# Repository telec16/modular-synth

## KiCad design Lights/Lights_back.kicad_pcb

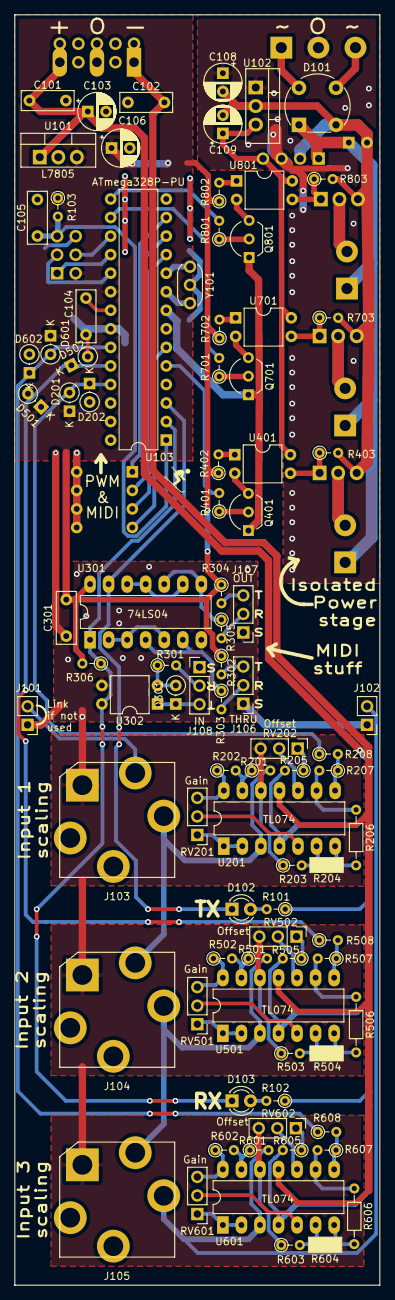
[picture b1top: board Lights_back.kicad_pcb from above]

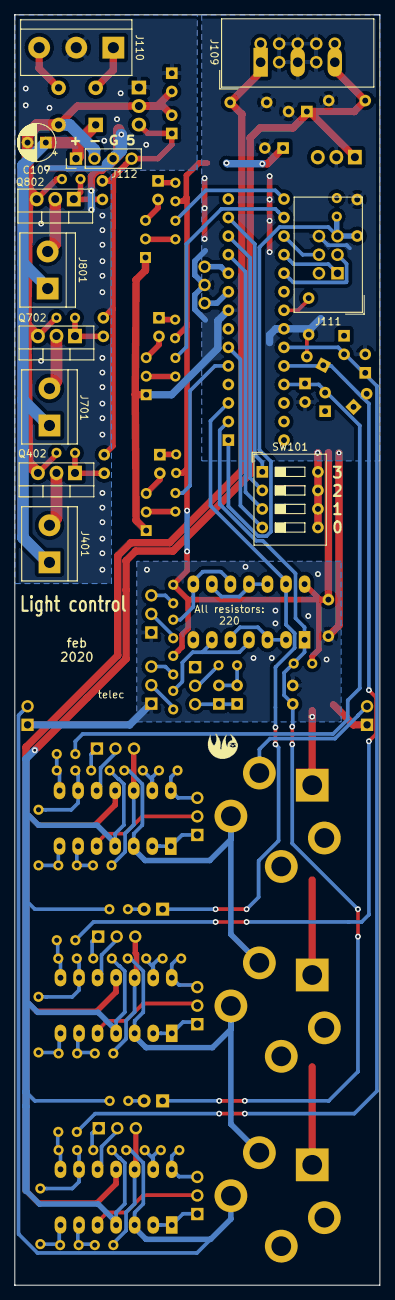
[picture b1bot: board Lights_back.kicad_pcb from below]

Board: 2 copper layers, 50.0 x 174.0 mm, 102 parts (12 on the bottom side), 91 nets.

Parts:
C101, C102, C104, C105, C301: 100n; C_Disc_D7.0mm_W2.5mm_P5.00mm
C103, C106, C108, C109: 1u; CP_Radial_D5.0mm_P2.50mm
C107: 10u; CP_Radial_D5.0mm_P2.50mm
D101: D_Bridge_+-AA; Diode_Bridge_Round_D8.9mm
D102, D103: LED; LED_D3.0mm_FlatTop
D201, D202, D301, D501, D502, D601, D602: 1N4148; D_DO-35_SOD27_P2.54mm_Vertical_KathodeUp
J101: chain_in; PinHeader_1x02_P2.54mm_Vertical
J102: chain_out; PinHeader_1x02_P2.54mm_Vertical
J103: Input1; Jack_6.35mm_PJ_629HAN
J104: Input2; Jack_6.35mm_PJ_629HAN
J105: Input3; Jack_6.35mm_PJ_629HAN
J106: THRU; PinHeader_TRS_P2.54mm_Vertical
J107: OUT; PinHeader_TRS_P2.54mm_Vertical
J108: IN; PinHeader_TRS_P2.54mm_Vertical
J109: EuroPower
J110: ExternalPower; TerminalBlock_bornier-3_P5.08mm
J111: Programming; IDC-Header_2x03_P2.54mm_Vertical
J112: chain_power; PinHeader_1x04_P2.54mm_Vertical
J401, J701, J801: Light; TerminalBlock_bornier-2_P5.08mm
Q401, Q701, Q801: PN2222A; TO-92_Inline_Wide
Q402, Q702, Q802: IRF540N; TO-220-3_Vertical
R101, R102: 1K; R_Axial_DIN0204_L3.6mm_D1.6mm_P2.54mm_Vertical
R103: 22k; R_Axial_DIN0204_L3.6mm_D1.6mm_P2.54mm_Vertical
R201, R202, R203, R205, R207, R501, R502, R503, R505, R507, R601, R602, R603, R605, R607: 100k; R_Axial_DIN0204_L3.6mm_D1.6mm_P2.54mm_Vertical
R204, R504, R604: 200k; R_Axial_DIN0204_L3.6mm_D1.6mm_P2.54mm_Vertical
R206, R506, R606: 100k; R_Axial_DIN0204_L3.6mm_D1.6mm_P7.62mm_Horizontal
R208, R401, R403, R508, R608, R701, R703, R801, R803: 1k; R_Axial_DIN0204_L3.6mm_D1.6mm_P2.54mm_Vertical
R301, R302, R303, R304, R305, R306: 220; R_Axial_DIN0204_L3.6mm_D1.6mm_P2.54mm_Vertical
R402, R702, R802: 100; R_Axial_DIN0204_L3.6mm_D1.6mm_P2.54mm_Vertical
RV201, RV202, RV501, RV502, RV601, RV602: 100k; PinHeader_1x03_P2.54mm_Vertical
SW101: MIDI_settings; SW_DIP_SPSTx04_Slide_9.78x12.34mm_W7.62mm_P2.54mm
U101, U102: L7805; TO-220-3_Vertical
U103: ATmega328P-PU; DIP-28_W7.62mm
U201, U501, U601: TL074; DIP-14_W7.62mm_LongPads
U301: 74LS04; DIP-14_W7.62mm_LongPads
U302, U401, U701, U801: 6N138; DIP-4_W7.62mm
Y101: 16MHz; Resonator-3Pin_W6.0mm_H3.0mm

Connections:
+5V: C106.1, C301.2, D201.1, D501.1, D601.1, J111.2, R103.1, R302.1, R304.1, R306.2, R402.1, R702.1, R802.1, U101.3, U103.7, U103.20, U301.14
+5VP: C109.1, J112.4, U102.3, U401.4, U701.4, U801.4
+12V: C101.2, C103.1, J109.3, R101.1, R102.1, R205.2, R505.2, R605.2, U101.1, U201.4, U501.4, U601.4
+VDC: C107.1, D101.1, J112.1, J401.1, J701.1, J801.1
-12V: C102.2, J109.1, U201.11, U501.11, U601.11
-VDC: C107.2, C108.2, C109.2, D101.2, J112.2, Q402.3, Q702.3, Q802.3, R403.2, R703.2, R803.2, U102.2
/ADC1: D201.2, D202.1, R208.1, U103.25
/ADC2: D501.2, D502.1, R508.1, U103.24
/ADC3: D601.2, D602.1, R608.1, U103.23
/MIDI/MIDI_IN+: D301.1, J108.T, U302.1
/MIDI/MIDI_IN-: J108.R, R301.2
/MIDI/MIDI_OUT+: J107.T, R304.2
/MIDI/MIDI_OUT-: J107.R, R305.2
/MIDI/MIDI_THRU+: J106.T, R302.2
/MIDI/MIDI_THRU-: J106.R, R303.2
/MIDI_IN: D103.1, R306.1, U103.2, U301.1, U302.4
/MIDI_OUT: D102.1, U103.3, U301.13
/MISO: J111.1, U103.18
/MOSI: J111.4, U103.17
/Normalize/In: J103.T, J104.TN, R201.2, U201.3
/PWM1: R801.2, U103.15
/PWM2: R701.2, U103.16
/PWM3: R401.2, U103.5
/SCK: J111.3, U103.19
/sheet606D67AE/In: J102.2, J105.T, R601.2, U601.3
/sheet606D2594/In: J104.T, J105.TN, R501.2, U501.3
/~RESET: C105.2, J111.5, R103.2, U103.1
GND: C101.1, C102.1, C103.2, C104.1, C105.1, C106.2, C301.1, D202.2, D502.2, D602.2, J101.1, J102.1, J103.S, J104.S, J105.S, J106.S, J107.S, J109.2, J111.6, Q401.1, Q701.1, Q801.1, R203.1, R503.1, R603.1, RV202.3, RV502.3, RV602.3, SW101.5, SW101.6, SW101.7, SW101.8, U101.2, U103.8, U103.22, U201.12, U301.7, U302.3, U501.12, U601.12, Y101.2
GNDPWR: C108.1, J110.2, J112.3, U102.1
unnamed: C104.2, U103.21
unnamed: D101.3, J110.3
unnamed: D101.4, J110.1
unnamed: D102.2, R101.2
unnamed: D103.2, R102.2
unnamed: D301.2, R301.1, U302.2
unnamed: J101.2, J103.TN
unnamed: J401.2, Q402.2
unnamed: J701.2, Q702.2
unnamed: J801.2, Q802.2
unnamed: Q401.2, R401.1
unnamed: Q401.3, U401.2
unnamed: Q402.1, R403.1, U401.3
unnamed: Q701.2, R701.1
unnamed: Q701.3, U701.2
unnamed: Q702.1, R703.1, U701.3
unnamed: Q801.2, R801.1
unnamed: Q801.3, U801.2
unnamed: Q802.1, R803.1, U801.3
unnamed: R201.1, R202.2, U201.13
unnamed: R202.1, RV201.3, U201.14
unnamed: R203.2, R204.1, U201.6
unnamed: R204.2, R206.2, U201.7
unnamed: R205.1, RV202.1
unnamed: R206.1, R207.2, U201.9
unnamed: R207.1, R208.2, U201.8
unnamed: R303.1, U301.4, U301.6
unnamed: R305.1, U301.8, U301.10
unnamed: R402.2, U401.1
unnamed: R501.1, R502.2, U501.13
unnamed: R502.1, RV501.3, U501.14
unnamed: R503.2, R504.1, U501.6
unnamed: R504.2, R506.2, U501.7
unnamed: R505.1, RV502.1
unnamed: R506.1, R507.2, U501.9
unnamed: R507.1, R508.2, U501.8
unnamed: R601.1, R602.2, U601.13
unnamed: R602.1, RV601.3, U601.14
unnamed: R603.2, R604.1, U601.6
unnamed: R604.2, R606.2, U601.7
unnamed: R605.1, RV602.1
unnamed: R606.1, R607.2, U601.9
unnamed: R607.1, R608.2, U601.8
unnamed: R702.2, U701.1
unnamed: R802.2, U801.1
unnamed: RV201.1, U201.1, U201.2
unnamed: RV201.2, U201.5
unnamed: RV202.2, U201.10
unnamed: RV501.1, U501.1, U501.2
unnamed: RV501.2, U501.5
unnamed: RV502.2, U501.10
unnamed: RV601.1, U601.1, U601.2
unnamed: RV601.2, U601.5
unnamed: RV602.2, U601.10
unnamed: SW101.1, U103.13
unnamed: SW101.2, U103.12
unnamed: SW101.3, U103.11
unnamed: SW101.4, U103.6
unnamed: U103.9, Y101.3
unnamed: U103.10, Y101.1
unnamed: U301.2, U301.3, U301.5
unnamed: U301.9, U301.11, U301.12

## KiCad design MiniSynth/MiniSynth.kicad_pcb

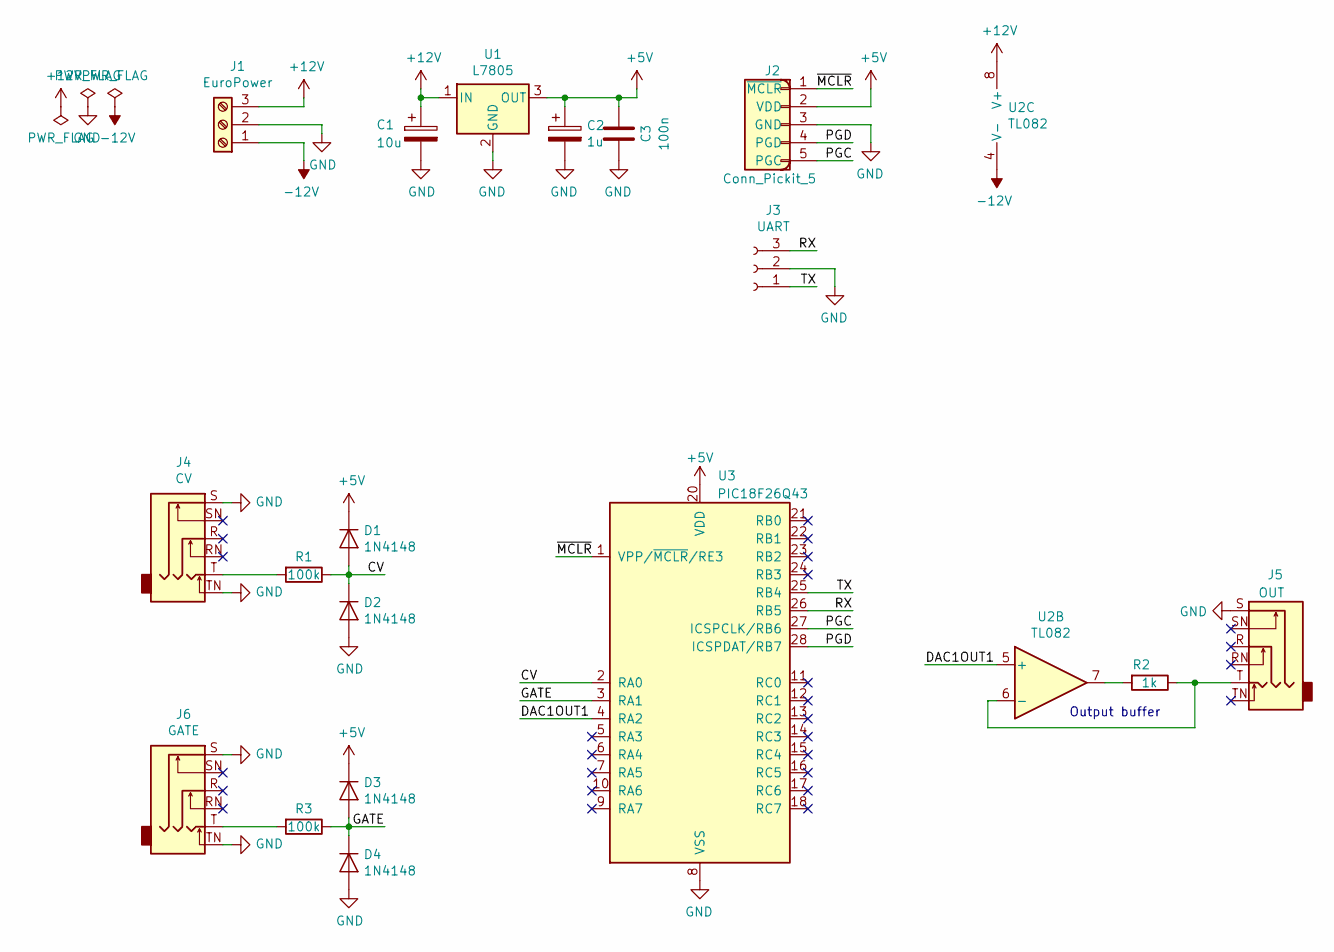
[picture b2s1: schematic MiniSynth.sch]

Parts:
C1: 10u; CP_Radial_D4.0mm_P1.50mm
C2: 1u; CP_Radial_D4.0mm_P1.50mm
C3: 100n; C_Disc_D7.0mm_W2.5mm_P5.00mm
D1, D2, D3, D4: 1N4148; D_DO-35_SOD27_P7.62mm_Horizontal
J1: EuroPower
J2: Conn_Pickit_5; PinHeader_1x05_P2.54mm_Vertical
J3: UART; PinSocket_1x03_P2.54mm_Vertical
J4: CV; PJ-611C
J5: OUT; PJ-611C
J6: GATE; PJ-611C
R1, R3: 100k; R_Axial_DIN0204_L3.6mm_D1.6mm_P7.62mm_Horizontal
R2: 1k; R_Axial_DIN0204_L3.6mm_D1.6mm_P7.62mm_Horizontal
U1: L7805; TO-220-3_Vertical
U2: TL082; SOIC-8_3.9x4.9mm_P1.27mm
U3: PIC18F26Q43; SOIC-28W_7.5x17.9mm_P1.27mm

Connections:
+5V: C2.1, C3.2, D1.1 (K), D3.1 (K), J2.2 (VDD), U1.3 (OUT), U3.20 (VDD)
+12V: C1.1, J1.3, U1.1 (IN), U2.8 (V+)
-12V: J1.1, U2.4 (V-)
/CV: D1.2 (A), D2.1 (K), R1.1, U3.2 (RA0)
/DAC1OUT1: U2.5 (+), U3.4 (RA2)
/GATE: D3.2 (A), D4.1 (K), R3.1, U3.3 (RA1)
/PGC: J2.5 (PGC), U3.27 (ICSPCLK/RB6)
/PGD: J2.4 (PGD), U3.28 (ICSPDAT/RB7)
/RX: J3.3, U3.26 (RB5)
/TX: J3.1, U3.25 (RB4)
/~MCLR: J2.1 (~MCLR), U3.1 (VPP/~MCLR~/RE3)
GND: C1.2, C2.2, C3.1, D2.2 (A), D4.2 (A), J1.2, J2.3 (GND), J3.2, J4.S, J4.TN, J5.S, J6.S, J6.TN, U1.2 (GND), U3.8 (VSS), U3.19 (VSS)
unnamed: J4.T, R1.2
unnamed: J5.T, R2.1, U2.6 (-)
unnamed: J6.T, R3.2
unnamed: R2.2, U2.7

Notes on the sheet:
Output buffer

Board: 2 copper layers, 19 parts (2 on the bottom side), 16 nets, no tracks yet.

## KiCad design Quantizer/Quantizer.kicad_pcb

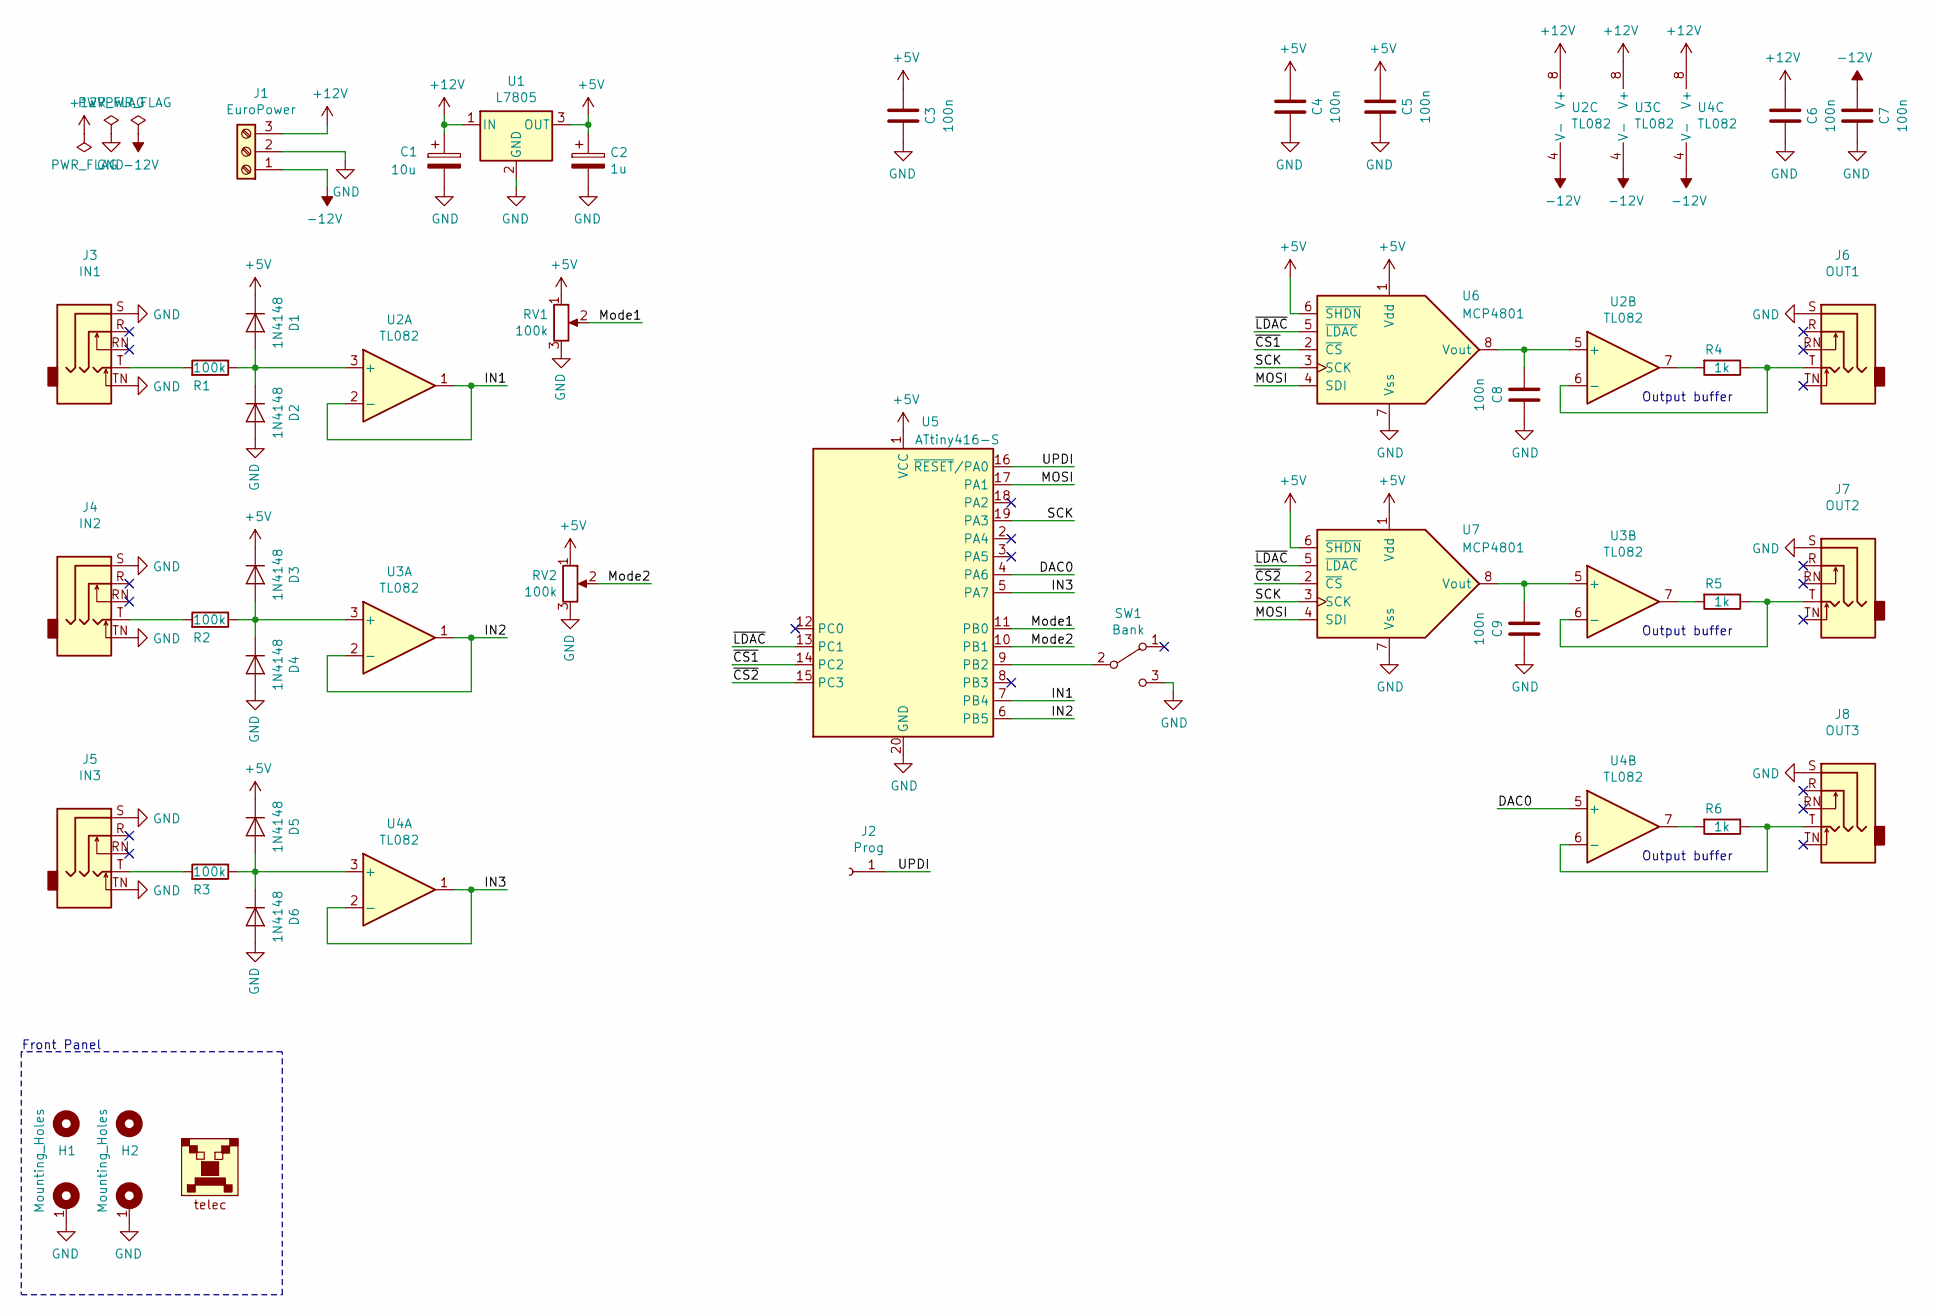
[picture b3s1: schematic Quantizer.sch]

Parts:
C1: 10u; CP_Radial_D4.0mm_P1.50mm
C2: 1u; CP_Radial_D4.0mm_P1.50mm
C3, C4, C5, C6, C7, C8, C9: 100n; C_1206_3216Metric_Pad1.42x1.75mm_HandSolder
D1, D2, D3, D4, D5, D6: 1N4148; D_1206_3216Metric_Pad1.42x1.75mm_HandSolder
H1, H2: Mounting_Holes; Kosmo_Panel_Dual_Mounting_Holes
J1: EuroPower
J2: Prog; TestPoint_Pad_D2.5mm
J3: IN1; Jack_Hole_Square
J4: IN2; Jack_Hole_Square
J5: IN3; Jack_Hole_Square
J6: OUT1; Jack_Hole_Square
J7: OUT2; Jack_Hole_Square
J8: OUT3; Jack_Hole_Square
LOGO1: telec; telec-8
R1, R2, R3: 100k; R_1206_3216Metric_Pad1.42x1.75mm_HandSolder
R4, R5, R6: 1k; R_1206_3216Metric_Pad1.42x1.75mm_HandSolder
RV1, RV2: 100k; Potentiometer_Alps_RK09K_Single_Vertical
SW1: Bank; PinHeader_1x03_P2.54mm_Vertical
U1: L7805; TO-220-3_Vertical
U2, U3, U4: TL082; SOIC-8_3.9x4.9mm_P1.27mm
U5: ATtiny416-S; SOIC-20W_7.5x12.8mm_P1.27mm
U6, U7: MCP4801; DIP-8_W7.62mm

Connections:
+5V: C2.1, C3.2, C4.2, C5.2, D1.1 (K), D3.1 (K), D5.1 (K), RV1.1, RV2.1, U1.3 (OUT), U5.1 (VCC), U6.1 (Vdd), U6.6 (~SHDN), U7.1 (Vdd), U7.6 (~SHDN)
+12V: C1.1, C6.2, J1.3, U1.1 (IN), U2.8 (V+), U3.8 (V+), U4.8 (V+)
-12V: C7.2, J1.1, U2.4 (V-), U3.4 (V-), U4.4 (V-)
/DAC0: U4.5 (+), U5.4 (PA6)
/IN1: U2.1, U2.2 (-), U5.7 (PB4)
/IN2: U3.1, U3.2 (-), U5.6 (PB5)
/IN3: U4.1, U4.2 (-), U5.5 (PA7)
/MOSI: U5.17 (PA1), U6.4 (SDI), U7.4 (SDI)
/Mode1: RV1.2, U5.11 (PB0)
/Mode2: RV2.2, U5.10 (PB1)
/SCK: U5.19 (PA3), U6.3 (SCK), U7.3 (SCK)
/UPDI: J2.1, U5.16 (~RESET~/PA0)
/~CS1: U5.14 (PC2), U6.2 (~CS)
/~CS2: U5.15 (PC3), U7.2 (~CS)
/~LDAC: U5.13 (PC1), U6.5 (~LDAC), U7.5 (~LDAC)
GND: C1.2, C2.2, C3.1, C4.1, C5.1, C6.1, C7.1, C8.1, C9.1, D2.2 (A), D4.2 (A), D6.2 (A), H1.1, H2.1, J1.2, J3.S, J3.TN, J4.S, J4.TN, J5.S, J5.TN, J6.S, J7.S, J8.S, RV1.3, RV2.3, SW1.3 (C), U1.2 (GND), U5.20 (GND), U6.7 (Vss), U7.7 (Vss)
unnamed: C8.2, U2.5 (+), U6.8 (Vout)
unnamed: C9.2, U3.5 (+), U7.8 (Vout)
unnamed: D1.2 (A), D2.1 (K), R1.1, U2.3 (+)
unnamed: D3.2 (A), D4.1 (K), R2.1, U3.3 (+)
unnamed: D5.2 (A), D6.1 (K), R3.1, U4.3 (+)
unnamed: J3.T, R1.2
unnamed: J4.T, R2.2
unnamed: J5.T, R3.2
unnamed: J6.T, R4.1, U2.6 (-)
unnamed: J7.T, R5.1, U3.6 (-)
unnamed: J8.T, R6.1, U4.6 (-)
unnamed: R4.2, U2.7
unnamed: R5.2, U3.7
unnamed: R6.2, U4.7
unnamed: SW1.2 (B), U5.9 (PB2)

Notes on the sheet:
Output buffer
Front Panel

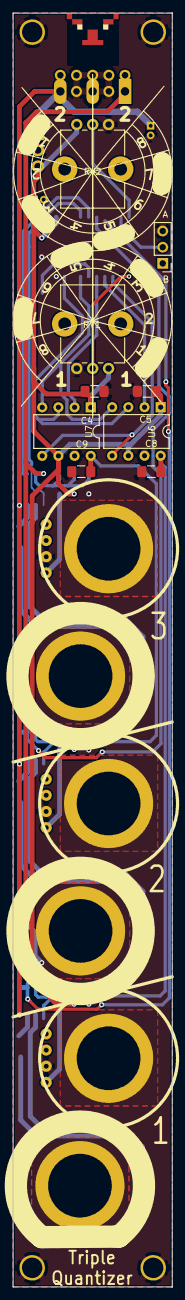
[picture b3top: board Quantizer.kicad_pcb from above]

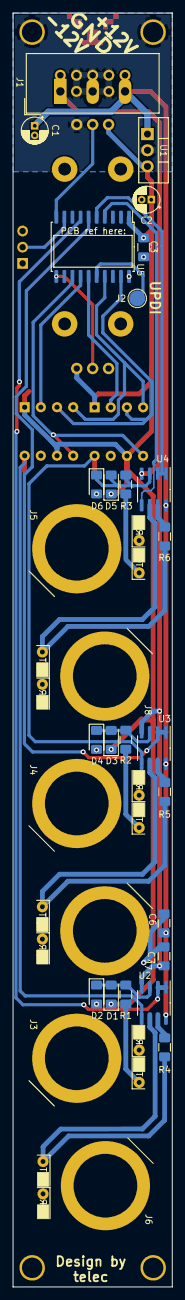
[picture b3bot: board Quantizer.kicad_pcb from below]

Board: 2 copper layers, 25.0 x 200.0 mm, 42 parts (24 on the bottom side), 31 nets.

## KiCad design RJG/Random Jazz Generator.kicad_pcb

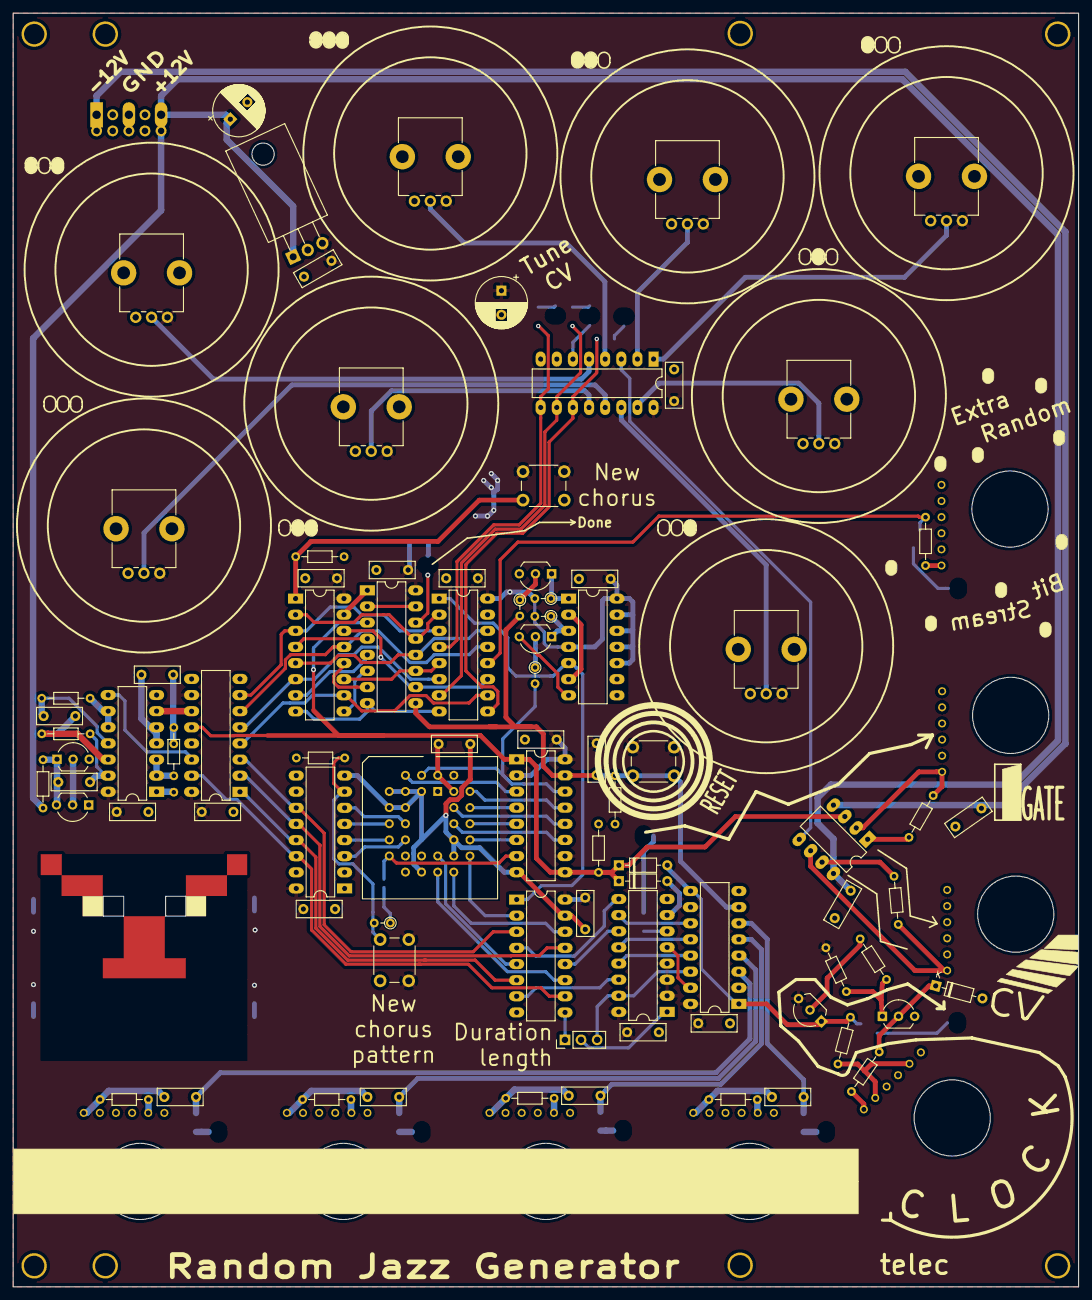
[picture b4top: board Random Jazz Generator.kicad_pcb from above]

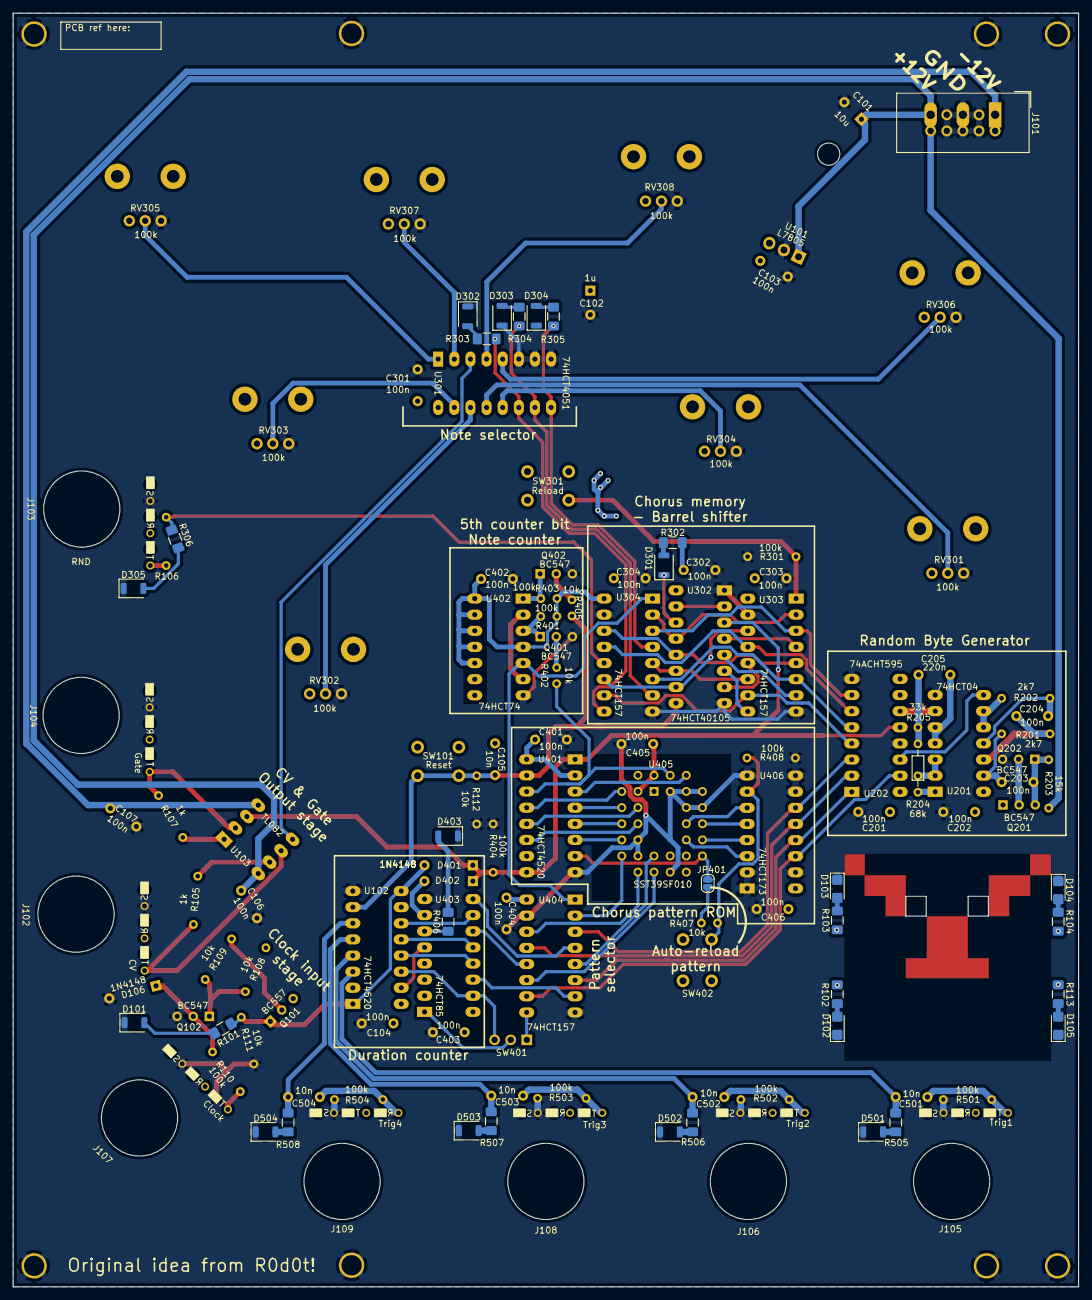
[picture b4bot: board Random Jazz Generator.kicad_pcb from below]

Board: 2 copper layers, 167.8 x 200.6 mm, 132 parts (33 on the bottom side), 120 nets.

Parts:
C101: 10u; CP_Radial_D8.0mm_P3.80mm
C102: 1u; CP_Radial_D8.0mm_P3.80mm
C103, C104, C106, C107, C201, C202, C203, C204, C301, C302, C303, C304, C401, C402, C403, C404, C405, C406: 100n; C_Disc_D7.0mm_W2.5mm_P5.00mm
C105, C501, C502, C503, C504: 10n; C_Disc_D7.0mm_W2.5mm_P5.00mm
C205: 220n; C_Disc_D7.0mm_W2.5mm_P5.00mm
D101, D301, D302, D303, D304, D305, D403, D501, D502, D503, D504: LED; LED_1206_3216Metric_ReverseMount_Hole1.8x2.4mm
D102, D103, D104, D105: LED; LED_1206_3216Metric_Castellated
D106, D401, D402: 1N4148; D_DO-35_SOD27_P7.62mm_Horizontal
H101, H102, H103, H104: Mounting_Holes; Kosmo_Panel_Dual_Mounting_Holes
J101: EuroPower
J102: CV; JackHole
J103: RND; JackHole
J104: Gate; JackHole
J105: Trig1; JackHole
J106: Trig2; JackHole
J107: Clock; JackHole
J108: Trig3; JackHole
J109: Trig4; JackHole
JP401: Auto-reload; SolderJumper-2_P1.3mm_Open_RoundedPad1.0x1.5mm
LOGO1: telec; telec-32
Q101: BC557; TO-92_Inline_Wide
Q102, Q201, Q202, Q401, Q402: BC547; TO-92_Inline_Wide
R101, R102, R103, R104, R113, R302, R303, R304, R305, R306, R406, R505, R506, R507, R508: 1k; R_1206_3216Metric_Pad1.42x1.75mm_HandSolder
R105, R106, R107: 1k; R_Axial_DIN0204_L3.6mm_D1.6mm_P7.62mm_Horizontal
R108, R109, R111, R112: 10k; R_Axial_DIN0204_L3.6mm_D1.6mm_P7.62mm_Horizontal
R110, R301, R404, R408, R501, R502, R503, R504: 100k; R_Axial_DIN0204_L3.6mm_D1.6mm_P7.62mm_Horizontal
R201, R202: 2k7; R_Axial_DIN0204_L3.6mm_D1.6mm_P7.62mm_Horizontal
R203: 15k; R_Axial_DIN0204_L3.6mm_D1.6mm_P7.62mm_Horizontal
R204: 68k; R_Axial_DIN0204_L3.6mm_D1.6mm_P7.62mm_Horizontal
R205: 33k; R_Axial_DIN0204_L3.6mm_D1.6mm_P7.62mm_Horizontal
R401, R403: 100k; R_Axial_DIN0204_L3.6mm_D1.6mm_P2.54mm_Vertical
R402, R405, R407: 10k; R_Axial_DIN0204_L3.6mm_D1.6mm_P2.54mm_Vertical
RV301, RV302, RV303, RV304, RV305, RV306, RV307, RV308: 100k; Potentiometer_Alps_RK09K_Single_Vertical
SW101: Reset; SW_PUSH_6mm
SW301, SW402: Reload; SW_PUSH_6mm
SW401: Duration Length; PinHeader_1x03_P2.54mm_Vertical
U101: L7805; TO-220-3_Horizontal_TabDown
U102, U401: 74HCT4520; DIP-16_W7.62mm_LongPads
U103: TL082; DIP-8_W7.62mm_LongPads
U201: 74HCT04; DIP-14_W7.62mm_LongPads
U202: 74ACHT595; DIP-16_W7.62mm_LongPads
U301: 74HCT4051; DIP-16_W7.62mm_LongPads
U302: 74HCT40105; DIP-16_W7.62mm_LongPads
U303, U304, U404: 74HCT157; DIP-16_W7.62mm_LongPads
U402: 74HCT74; DIP-14_W7.62mm_LongPads
U403: 74HCT85; DIP-16_W7.62mm_LongPads
U405: SST39SF010; PLCC-32_THT-Socket
U406: 74HCT173; DIP-16_W7.62mm_LongPads

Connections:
+5V: C102.1, C103.2, C104.2, C105.2, C201.2, C202.2, C301.2, C302.2, C303.2, C304.2, C401.2, C402.2, C403.2, C404.2, C405.2, C406.2, Q101.3, R102.1, R103.1, R104.1, R108.2, R113.1, R302.1, R401.2, R403.2, RV301.1, RV302.1, RV303.1, RV304.1, RV305.1, RV306.1, RV307.1, RV308.1, SW101.1, SW301.1, SW402.1, U101.3, U102.2, U102.10, U102.16, U201.14, U202.10, U202.16, U301.16, U302.16, U303.16, U304.16, U401.2, U401.10, U401.16, U402.4, U402.10, U402.11, U402.12, U402.13, U402.14, U403.2, U403.3, U403.4, U403.16, U404.16, U405.31, U405.32, U406.16
+12V: C101.1, C106.2, J101.3, R203.1, U101.1, U103.8
-12V: C107.2, J101.1, U103.4
/Clk: D401.2, Q101.1, R101.1, R111.2, U102.1, U102.9
/Duration/End: R406.1, U403.6
/Duration/Overflow: U102.15, U403.5
/Duration/~Chorus~\Impro: U304.1, U402.5, U404.1
/Gate: D401.1, D402.1, R404.1, U103.3, U202.12, U302.3, U401.1, U401.9
/Notes/CV: U103.5, U301.3
/Notes/CV1: RV301.2, U301.13
/Notes/CV2: RV302.2, U301.14
/Notes/CV3: RV303.2, U301.15
/Notes/CV4: RV304.2, U301.12
/Notes/CV5: RV305.2, U301.1
/Notes/CV6: RV306.2, U301.5
/Notes/CV7: RV307.2, U301.2
/Notes/CV8: RV308.2, U301.4
/Notes/Chorus1: U302.13, U303.2, U304.2
/Notes/Chorus2: U302.12, U303.5, U304.14
/Notes/Chorus3: U302.11, U303.11, U304.5
/Notes/Chorus4: U302.10, U303.14, U304.11
/Notes/Full: D301.1, U302.14
/Notes/RND: R106.2, R306.1, U304.12
/Notes/Reload: R301.1, SW301.2, U303.1
/Notes/S0: R303.1, U301.11, U304.9
/Notes/S1: R304.1, U301.10, U304.7
/Notes/S2: R305.1, U301.9, U304.4
/RB0: U202.15, U404.10, U406.14
/RB1: U202.1, U404.6, U406.13
/RB2: U202.2, U404.13, U406.12
/RB3: U202.3, U404.3, U406.11
/RB4: U202.4, U303.10, U304.10
/RB5: U202.5, U303.6, U304.6
/RB6: U202.6, U303.13, U304.13
/RB7: U202.7, U303.3, U304.3
/RandomByteGenerator/Fclk: U201.6, U202.11
/RandomByteGenerator/Rb: U201.8, U202.14
/Rst: C105.1, R112.1, R405.2, SW101.2, U102.7, U302.9, U401.15
/Trig1: C501.2, J105.T, R501.1
/Trig2: C502.2, J106.T, R502.1
/Trig3: C503.1, J108.T, R503.1
/Trig4: C504.1, J109.T, R504.1
GND: C101.2, C102.2, C103.1, C104.1, C106.1, C107.1, C201.1, C202.1, C301.1, C302.1, C303.1, C304.1, C401.1, C402.1, C403.1, C404.1, C405.1, C406.1, D101.1, D102.1, D103.1, D104.1, D105.1, D106.2, D302.1, D303.1, D304.1, D305.1, D403.1, D501.1, D502.1, D503.1, D504.1, H101.1, H102.1, H103.1, H104.1, J101.2, J102.S, J103.S, J104.S, J105.S, J106.S, J107.S, J107.TN, J108.S, J109.S, Q102.3, Q202.3, Q401.3, Q402.3, R111.1, R112.2, R301.2, R404.2, R408.2, R501.2, R502.2, R503.2, R504.2, RV301.3, RV302.3, RV303.3, RV304.3, RV305.3, RV306.3, RV307.3, RV308.3, U101.2, U102.8, U201.7, U202.8, U202.13, U301.6, U301.7, U301.8, U302.1, U302.8, U303.8, U303.15, U304.8, U304.15, U401.8, U402.7, U403.8, U404.8, U404.15, U405.3, U405.5, U405.6, U405.7, U405.8, U405.16, U405.22, U405.24, U406.1, U406.2, U406.8, U406.9, U406.10, U406.15
unnamed: C203.1, R201.1, U201.13
unnamed: C203.2, Q201.3, Q202.1, R203.2
unnamed: C204.1, R202.1, U201.11
unnamed: C204.2, R201.2, U201.12
unnamed: C205.1, U201.4, U201.5
unnamed: C205.2, R204.2, R205.2
unnamed: C501.1, R505.1, U102.3
unnamed: C502.1, R506.1, U102.4
unnamed: C503.2, R507.1, U102.5
unnamed: C504.2, R508.1, U102.6
unnamed: D101.2, R101.2
unnamed: D102.2, R102.2
unnamed: D103.2, R103.2
unnamed: D104.2, R104.2
unnamed: D105.2, R113.2
unnamed: D106.1, Q102.2, R110.1
unnamed: D301.2, R302.2
unnamed: D302.2, R303.2
unnamed: D303.2, R304.2
unnamed: D304.2, R305.2
unnamed: D305.2, R306.2
unnamed: D402.2, U403.7
unnamed: D403.2, R406.2
unnamed: D501.2, R505.2
unnamed: D502.2, R506.2
unnamed: D503.2, R507.2
unnamed: D504.2, R508.2
unnamed: J102.T, R105.1, U103.6
unnamed: J103.T, R106.1
unnamed: J104.T, R107.1, U103.2
unnamed: J107.T, R110.2
unnamed: JP401.1, U401.7, U405.13
unnamed: JP401.2, R407.1
unnamed: Q101.2, R109.1
unnamed: Q102.1, R108.1, R109.2
unnamed: Q201.2, Q202.2
unnamed: Q401.1, R401.1, U402.3
unnamed: Q401.2, R402.1
unnamed: Q402.1, R403.1, U402.1
unnamed: Q402.2, R405.1
unnamed: R105.2, U103.7
unnamed: R107.2, U103.1
unnamed: R202.2, U201.9, U201.10
unnamed: R204.1, U201.1
unnamed: R205.1, U201.2, U201.3
unnamed: R402.2, U401.14, U405.2
unnamed: R407.2, R408.1, SW402.2, U406.7
unnamed: SW401.1, U404.9
unnamed: SW401.2, U403.1
unnamed: SW401.3, U102.14, U403.15
unnamed: U102.11, U403.10
unnamed: U102.12, U403.12
unnamed: U102.13, U403.13
unnamed: U302.4, U303.4
unnamed: U302.5, U303.7
unnamed: U302.6, U303.9
unnamed: U302.7, U303.12
unnamed: U302.2, U302.15
unnamed: U401.3, U405.4
unnamed: U401.4, U405.27
unnamed: U401.5, U405.25
unnamed: U401.6, U405.23
unnamed: U401.11, U405.26
unnamed: U401.12, U405.28
unnamed: U401.13, U405.29
unnamed: U402.2, U402.6
unnamed: U403.9, U404.4
unnamed: U403.11, U404.12
unnamed: U403.14, U404.7
unnamed: U404.2, U405.21
unnamed: U404.5, U405.19
unnamed: U404.11, U405.18
unnamed: U404.14, U405.20
unnamed: U405.9, U406.5
unnamed: U405.10, U406.6
unnamed: U405.11, U406.4
unnamed: U405.12, U406.3
